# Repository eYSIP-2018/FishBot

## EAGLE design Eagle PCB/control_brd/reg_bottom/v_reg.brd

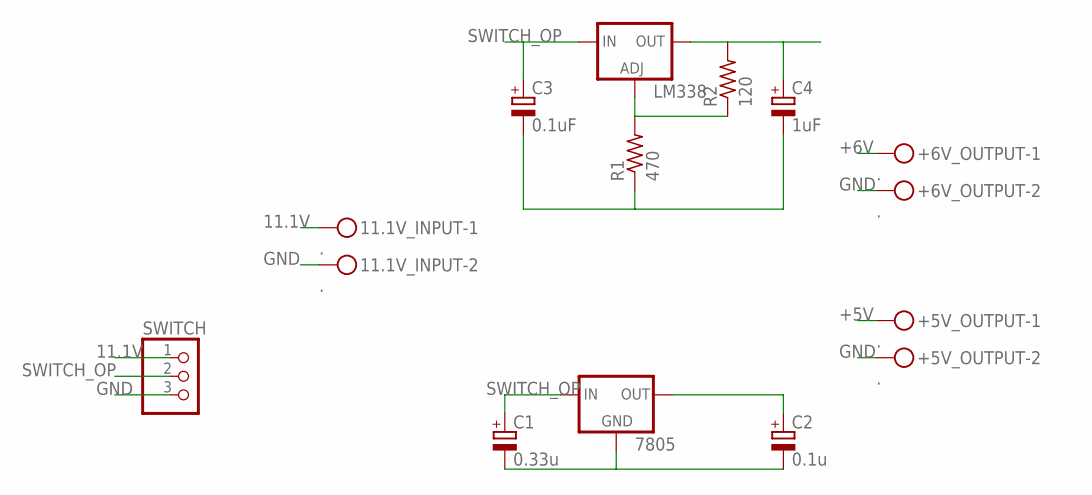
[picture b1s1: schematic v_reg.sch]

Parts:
11.1V_INPUT: .; MKDSN1,5/2-5,08
7805: 78XXS
+5V_OUTPUT, +6V_OUTPUT: .; MKDSN1,5/2-5,08
C1: 0.33u; E1,8-4
C2: 0.1u; E1,8-4
C3: 0.1uF; E1,8-4
C4: 1uF; E1,8-4
LM338: LM138-TS; TO220S
R1: 470; 0309/10
R2: 120; 0309/10
SWITCH: PINHD-1X3; 1X03

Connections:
11.1V: 11.1V_INPUT.1, SWITCH.1
+5V: 7805.OUT, +5V_OUTPUT.1, C2.+
+6V: +6V_OUTPUT.1, C4.+, LM338.2 (OUT), R2.2
GND: 11.1V_INPUT.2, 7805.GND, +5V_OUTPUT.2, +6V_OUTPUT.2, C1.-, C2.-, C3.-, C4.-, R1.1, SWITCH.3
unnamed: LM338.1 (ADJ), R1.2, R2.1
SWITCH_OP: 7805.IN, C1.+, C3.+, LM338.3 (IN), SWITCH.2

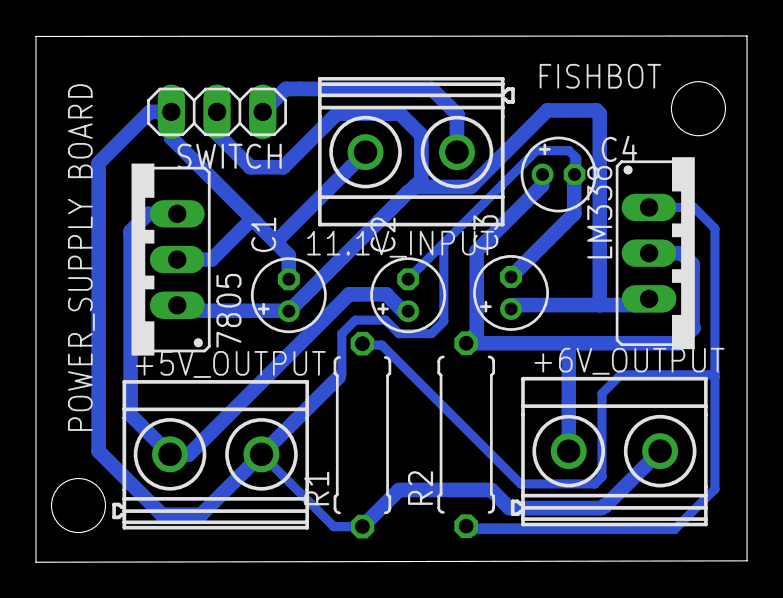
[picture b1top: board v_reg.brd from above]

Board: 2 copper layers, 39.5 x 29.2 mm, 12 parts (0 on the bottom side), 6 nets.

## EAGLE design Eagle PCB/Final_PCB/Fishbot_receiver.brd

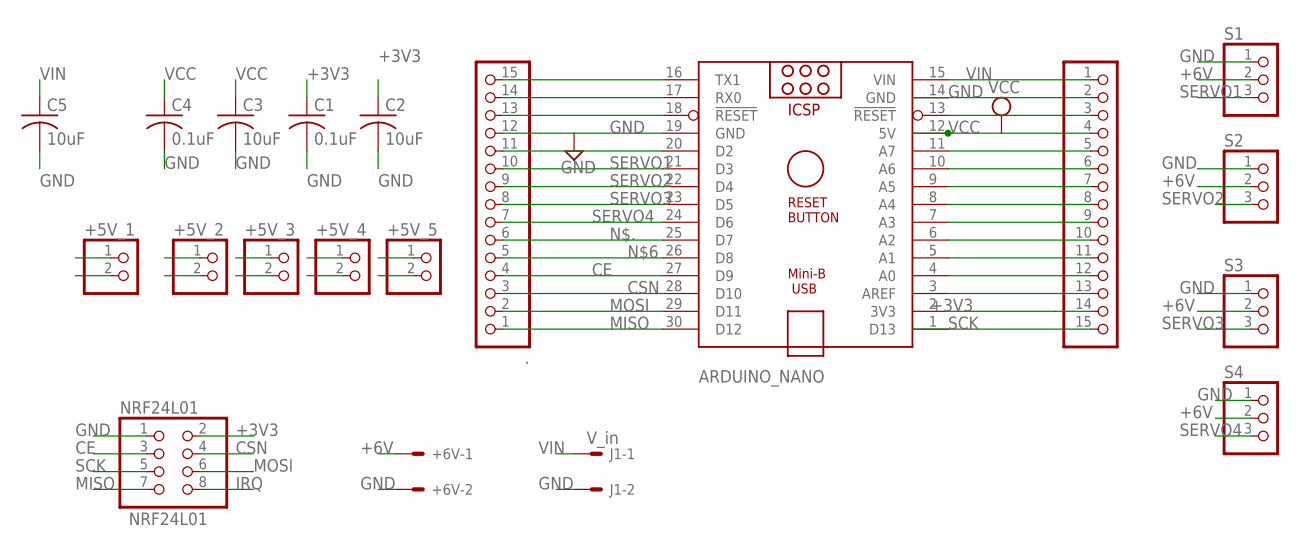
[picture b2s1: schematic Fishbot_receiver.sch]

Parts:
+5V_1, +5V_2, +5V_3, +5V_4, +5V_5: PINHD-1X2; 1X02
+6V: 22-27-2021-02; 6410-02
.: PINHD-1X15; 1X15
ARDUINO_NANO: ARDUINO_NANO
C1, C4: 0.1uF; C1206
C2, C3, C5: 10uF; C1206
J1: V_in; 6410-02
NRF24L01: PINHD-2X4; 2X04
S1, S2, S3, S4: PINHD-1X3; 1X03
_: PINHD-1X15; 1X15

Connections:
+3V3: ARDUINO_NANO.2 (3V3), C1.1, C2.1, NRF24L01.2, _.14
+6V: +6V.1, S1.2, S2.2, S3.2, S4.2
CE: ..4, ARDUINO_NANO.27 (D9), NRF24L01.3
CSN: ..3, ARDUINO_NANO.28 (D10), NRF24L01.4
GND: +5V_1.2, +5V_2.2, +5V_3.2, +5V_4.2, +5V_5.2, +6V.2, ..12, ARDUINO_NANO.14 (GND), ARDUINO_NANO.19 (GND), C1.2, C2.2, C3.2, C4.2, C5.2, J1.2, NRF24L01.1, S1.1, S2.1, S3.1, S4.1, _.2
IRQ: NRF24L01.8
MISO: ..1, ARDUINO_NANO.30 (D12), NRF24L01.7
MOSI: ..2, ARDUINO_NANO.29 (D11), NRF24L01.6
unnamed: ..5, ARDUINO_NANO.26 (D8)
unnamed: ..11, ARDUINO_NANO.20 (D2)
unnamed: ..13, ARDUINO_NANO.18 (!RESET)
unnamed: ..14, ARDUINO_NANO.17 (RX0)
unnamed: ..15, ARDUINO_NANO.16 (TX1)
unnamed: ARDUINO_NANO.13 (!RESET), _.3
unnamed: ARDUINO_NANO.11 (A7), _.5
unnamed: ARDUINO_NANO.10 (A6), _.6
unnamed: ARDUINO_NANO.9 (A5), _.7
unnamed: ARDUINO_NANO.8 (A4), _.8
unnamed: ARDUINO_NANO.7 (A3), _.9
unnamed: ARDUINO_NANO.6 (A2), _.10
unnamed: ARDUINO_NANO.5 (A1), _.11
unnamed: ARDUINO_NANO.4 (A0), _.12
unnamed: ARDUINO_NANO.3 (AREF), _.13
N$.: ..6, ARDUINO_NANO.25 (D7)
SCK: ARDUINO_NANO.1 (D13), NRF24L01.5, _.15
SERVO1: ..10, ARDUINO_NANO.21 (D3), S1.3
SERVO2: ..9, ARDUINO_NANO.22 (D4), S2.3
SERVO3: ..8, ARDUINO_NANO.23 (D5), S3.3
SERVO4: ..7, ARDUINO_NANO.24 (D6), S4.3
VCC: +5V_1.1, +5V_2.1, +5V_3.1, +5V_4.1, +5V_5.1, ARDUINO_NANO.12 (5V), C3.1, C4.1, _.4
VIN: ARDUINO_NANO.15 (VIN), C5.1, J1.1, _.1

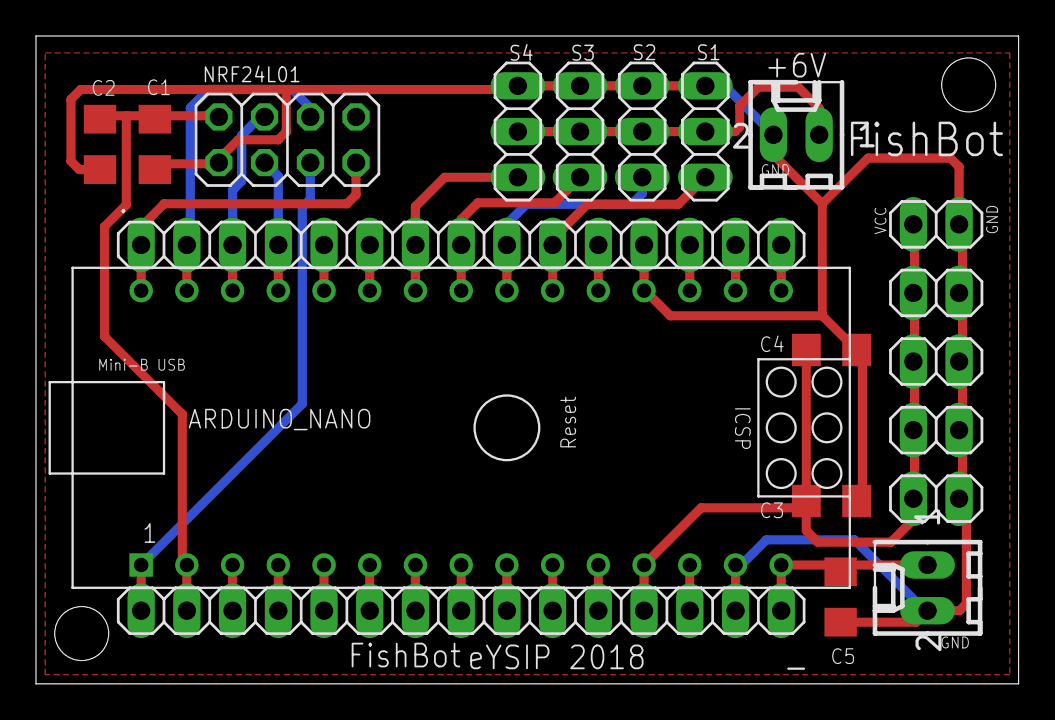
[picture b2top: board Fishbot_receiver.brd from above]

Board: 2 copper layers, 54.6 x 36.0 mm, 20 parts (0 on the bottom side), 30 nets.

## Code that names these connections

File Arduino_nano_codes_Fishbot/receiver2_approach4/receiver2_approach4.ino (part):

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#include <math.h>
#include<Servo.h>

#define servo1 5
#define servo2 6
#define servo3 9
#define servo4 10

Servo servo_1;
Servo servo_2;
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
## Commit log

2018-06-11 CAD files
2018-06-12 Sorted
2018-06-12 12-06-2018
2018-06-16 16-06-2018
2018-06-21 Arduino Nano files
2018-06-22 Progress ppt 2
2018-06-25 Eagle PCB Design
2018-06-25 PCB with jack
2018-06-25 Fritzing recv circuit
2018-06-25 25-6-18
2018-06-26 Transmitter schematic
2018-06-27 Final Eagle files
2018-07-06 Final PCB files
2018-07-06 6-7-18
2018-07-06 Final Codes with comment
